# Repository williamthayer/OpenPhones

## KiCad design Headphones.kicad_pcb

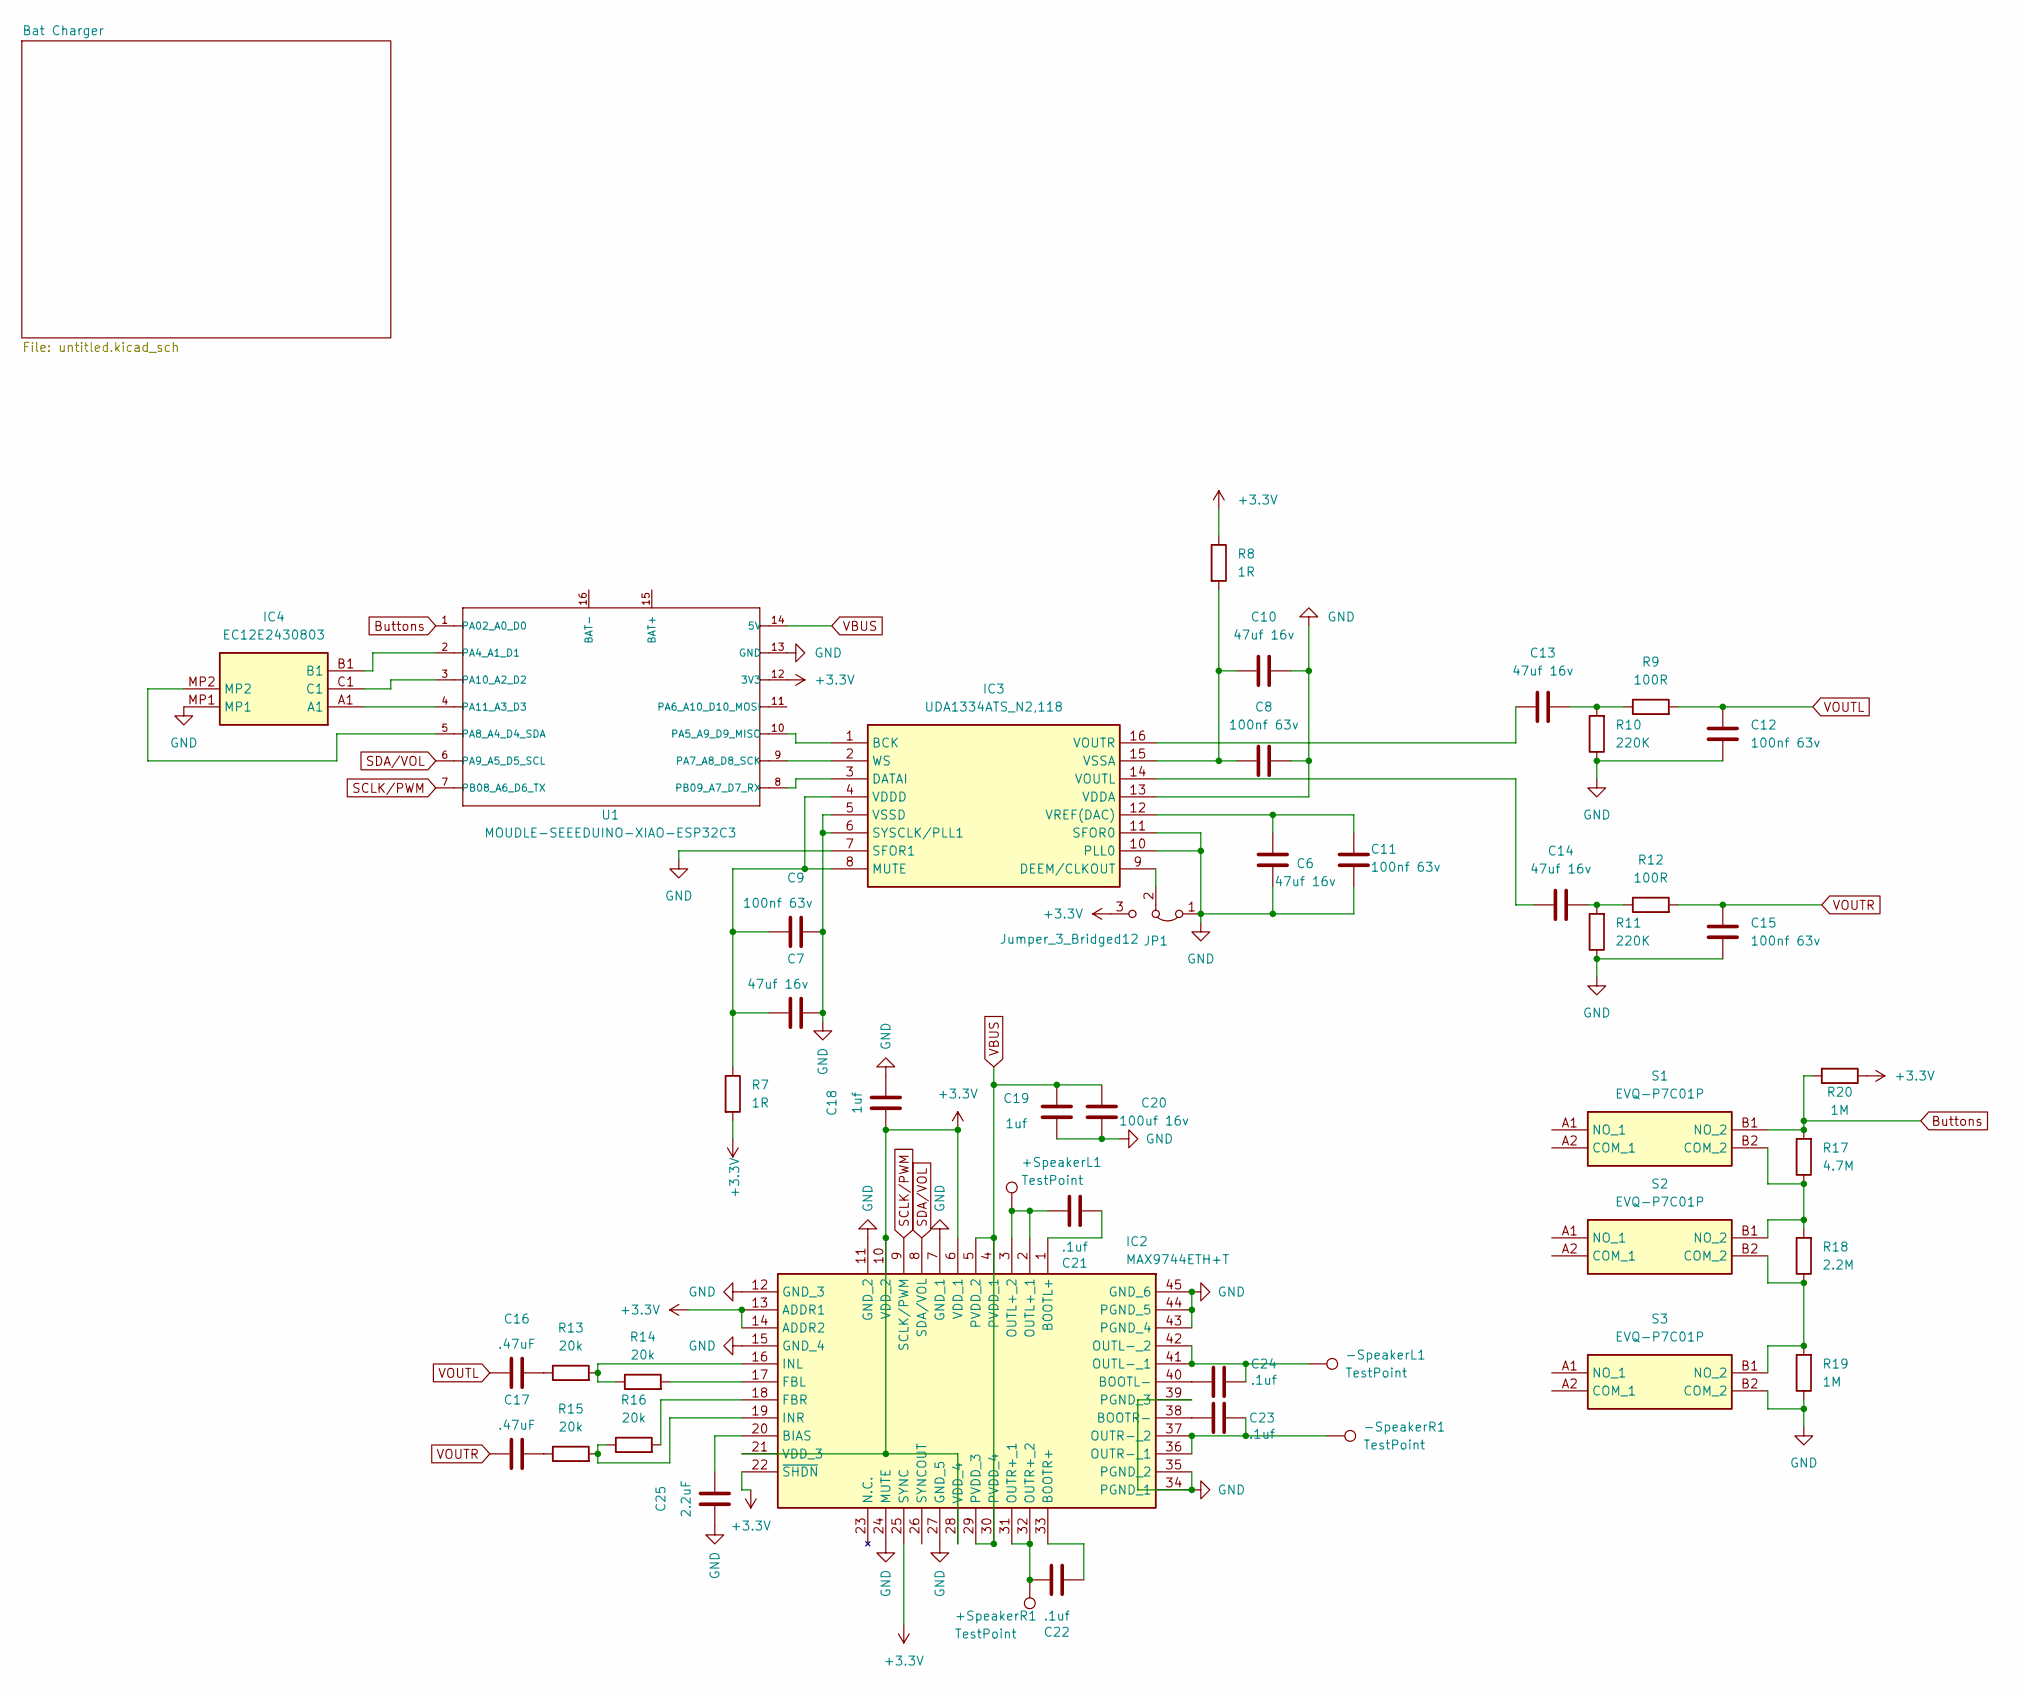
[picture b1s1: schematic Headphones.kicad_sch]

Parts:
+SpeakerL1: TestPoint; TestPoint_Loop_D1.80mm_Drill1.0mm_Beaded
+SpeakerR1: TestPoint; TestPoint_Loop_D1.80mm_Drill1.0mm_Beaded
-SpeakerL1: TestPoint; TestPoint_Loop_D1.80mm_Drill1.0mm_Beaded
-SpeakerR1: TestPoint; TestPoint_Loop_D1.80mm_Drill1.0mm_Beaded
C6, C7, C10, C13, C14: 47uf 16v; C_1210_3225Metric
C8, C9, C11, C12, C15: 100nf 63v; C_0805_2012Metric
C16, C17: .47uF; C_0805_2012Metric
C18, C19: 1uf; C_0805_2012Metric
C20: 100uf 16v; C_1210_3225Metric
C21, C22, C23, C24: .1uf; C_0805_2012Metric
C25: 2.2uF; C_0805_2012Metric
IC2: MAX9744ETH+T; QFN50P700X700X80-45N; Manufacturer_Part_Number MAX9744ETH+T; Mouser Part Number 700-MAX9744ETH+T
IC3: UDA1334ATS_N2,118; SOP65P640X150-16N; Manufacturer_Part_Number UDA1334ATS/N2,118; Mouser Part Number 771-UDA1334ATSDH-T
IC4: EC12E2430803; Manufacturer_Part_Number EC12E2430803; Mouser Part Number 688-EC12E2430803
JP1: Jumper_3_Bridged12; SolderJumper-3_P1.3mm_Bridged2Bar12_Pad1.0x1.5mm
R7, R8: 1R; R_0805_2012Metric
R9, R12: 100R; R_0805_2012Metric
R10, R11: 220K; R_0805_2012Metric
R13, R14, R15, R16: 20k; R_0805_2012Metric
R17: 4.7M; R_0805_2012Metric
R18: 2.2M; R_0805_2012Metric
R19, R20: 1M; R_0805_2012Metric
S1, S2, S3: EVQ-P7C01P; EVQP7C01P; Manufacturer_Part_Number EVQ-P7C01P; Mouser Part Number 667-EVQP7C01P
U1: MOUDLE-SEEEDUINO-XIAO-ESP32C3; MOUDLE14P-SMD-2.54-21X17.8MM

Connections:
+3.3V: C18.1, IC2.6 (VDD_1), IC2.10 (VDD_2), IC2.13 (ADDR1), IC2.14 (ADDR2), IC2.21 (VDD_3), IC2.22 (~SHDN), IC2.25 (SYNC), IC2.28 (VDD_4), JP1.3 (B), R7.2, R8.1, R20.1, U1.12 (3V3)
Buttons: R17.2, R20.2, S1.B1 (NO_2), U1.1 (PA02_A0_D0)
GND: C6.1, C7.2, C8.2, C9.2, C10.2, C11.1, C12.1, C15.1, C18.2, C19.1, C20.1, C25.1, IC2.7 (GND_1), IC2.11 (GND_2), IC2.12 (GND_3), IC2.15 (GND_4), IC2.24 (MUTE), IC2.27 (GND_5), IC2.34 (PGND_1), IC2.35 (PGND_2), IC2.39 (PGND_3), IC2.43 (PGND_4), IC2.44 (PGND_5), IC2.45 (GND_6), IC3.5 (VSSD), IC3.6 (SYSCLK/PLL1), IC3.7 (SFOR1), IC3.10 (PLL0), IC3.11 (SFOR0), IC3.13 (VDDA), IC4.MP1, JP1.1 (A), R10.1, R11.1, R19.1, S3.B2 (COM_2), U1.13 (GND); also elsewhere on the board
unnamed: C13.2, R9.1, R10.2
unnamed: C14.2, R11.2, R12.1
unnamed: C16.2, R13.1
unnamed: C17.2, R15.1
unnamed: C25.2, IC2.20 (BIAS)
unnamed: C21.1, IC2.1 (BOOTL+)
unnamed: C24.1, IC2.40 (BOOTL-)
unnamed: C22.1, IC2.33 (BOOTR+)
unnamed: C23.1, IC2.38 (BOOTR-)
unnamed: IC2.17 (FBL), R14.2
unnamed: IC2.18 (FBR), R16.2
unnamed: IC2.16 (INL), R13.2, R14.1
unnamed: IC2.19 (INR), R15.2, R16.1
unnamed: +SpeakerL1.1, C21.2, IC2.2 (OUTL+_1), IC2.3 (OUTL+_2)
unnamed: -SpeakerL1.1, C24.2, IC2.41 (OUTL-_1), IC2.42 (OUTL-_2)
unnamed: +SpeakerR1.1, C22.2, IC2.31 (OUTR+_1), IC2.32 (OUTR+_2)
unnamed: -SpeakerR1.1, C23.2, IC2.36 (OUTR-_1), IC2.37 (OUTR-_2)
unnamed: IC3.1 (BCK), U1.10 (PA5_A9_D9_MISO)
unnamed: IC3.3 (DATAI), U1.8 (PB09_A7_D7_RX)
unnamed: IC3.9 (DEEM/CLKOUT), JP1.2 (C)
unnamed: C7.1, C9.1, IC3.4 (VDDD), IC3.8 (MUTE), R7.1
unnamed: C14.1, IC3.14 (VOUTL)
unnamed: C13.1, IC3.16 (VOUTR)
unnamed: C6.2, C11.2, IC3.12 (VREF(DAC))
unnamed: C8.1, C10.1, IC3.15 (VSSA), R8.2
unnamed: IC3.2 (WS), U1.9 (PA7_A8_D8_SCK)
unnamed: R17.1, R18.2, S1.B2 (COM_2), S2.B1 (NO_2)
unnamed: R18.1, R19.2, S2.B2 (COM_2), S3.B1 (NO_2)
unnamed: IC4.B1, U1.2 (PA4_A1_D1)
unnamed: IC4.MP2, U1.5 (PA8_A4_D4_SDA)
unnamed: IC4.C1, U1.3 (PA10_A2_D2)
unnamed: IC4.A1, U1.4 (PA11_A3_D3)
SCLK/PWM: IC2.9 (SCLK/PWM), U1.7 (PB08_A6_D6_TX)
SDA/VOL: IC2.8 (SDA/VOL), U1.6 (PA9_A5_D5_SCL)
VBUS: C19.2, C20.2, IC2.4 (PVDD_1), IC2.5 (PVDD_2), IC2.29 (PVDD_3), IC2.30 (PVDD_4), U1.14 (5V); also elsewhere on the board
VOUTL: C12.2, C16.1, R9.2
VOUTR: C15.2, C17.1, R12.2

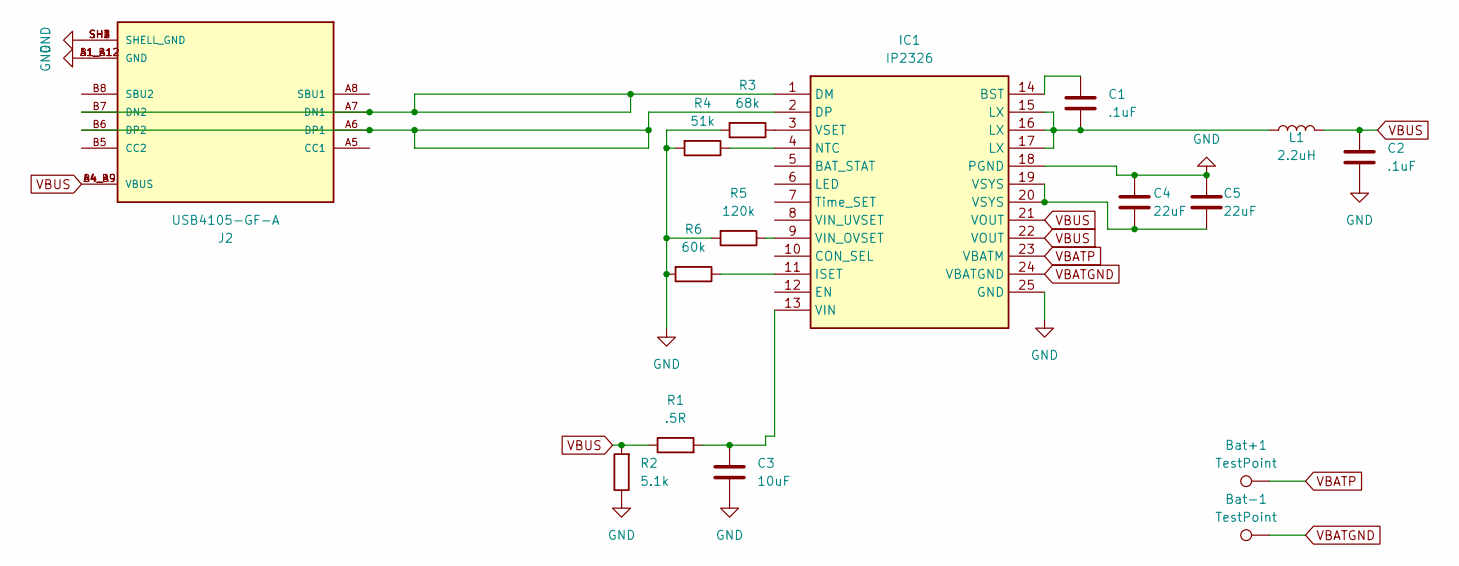
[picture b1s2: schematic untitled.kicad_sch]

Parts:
Bat+1: TestPoint; TestPoint_Loop_D1.80mm_Drill1.0mm_Beaded
Bat-1: TestPoint; TestPoint_Loop_D1.80mm_Drill1.0mm_Beaded
C1, C2: .1uF; C_0805_2012Metric
C3: 10uF; C_0805_2012Metric
C4, C5: 22uF; C_0805_2012Metric
IC1: IP2326; HVQFN-24-1EP_4x4mm_P0.5mm_EP2.5x2.5mm; Mouser Part Number 634-LB10F16ES1CFN24R
J2: USB4105-GF-A; GCT_USB4105-GF-A; PARTREV B4
L1: 2.2uH; L_0805_2012Metric
R1: .5R; R_0805_2012Metric
R2: 5.1k; R_0805_2012Metric
R3: 68k; R_0805_2012Metric
R4: 51k; R_0805_2012Metric
R5: 120k; R_0805_2012Metric
R6: 60k; R_0805_2012Metric

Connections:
GND: C2.2, C3.2, C4.1, C5.1, IC1.18 (PGND), IC1.25 (GND), J2.A1_B12 (GND), J2.B1_A12 (GND), J2.SH1 (SHELL_GND), J2.SH2 (SHELL_GND), J2.SH3 (SHELL_GND), J2.SH4 (SHELL_GND), R2.1, R3.2, R4.2, R5.2, R6.2; also elsewhere on the board
unnamed: C1.2, IC1.15 (LX), IC1.16 (LX), IC1.17 (LX), L1.1
unnamed: C4.2, C5.2, IC1.19 (VSYS), IC1.20 (VSYS)
unnamed: C1.1, IC1.14 (BST)
unnamed: IC1.1 (DM), J2.A7 (DN1), J2.B7 (DN2)
unnamed: IC1.2 (DP), J2.A6 (DP1), J2.B6 (DP2)
unnamed: IC1.11 (ISET), R6.1
unnamed: IC1.4 (NTC), R4.1
unnamed: C3.1, IC1.13 (VIN), R1.2
unnamed: IC1.9 (VIN_OVSET), R5.1
unnamed: IC1.3 (VSET), R3.1
VBATGND: Bat-1.1, IC1.24 (VBATGND)
VBATP: Bat+1.1, IC1.23 (VBATM)
VBUS: C2.1, IC1.21 (VOUT), IC1.22 (VOUT), J2.A4_B9 (VBUS), J2.B4_A9 (VBUS), L1.2, R1.1, R2.2; also elsewhere on the board

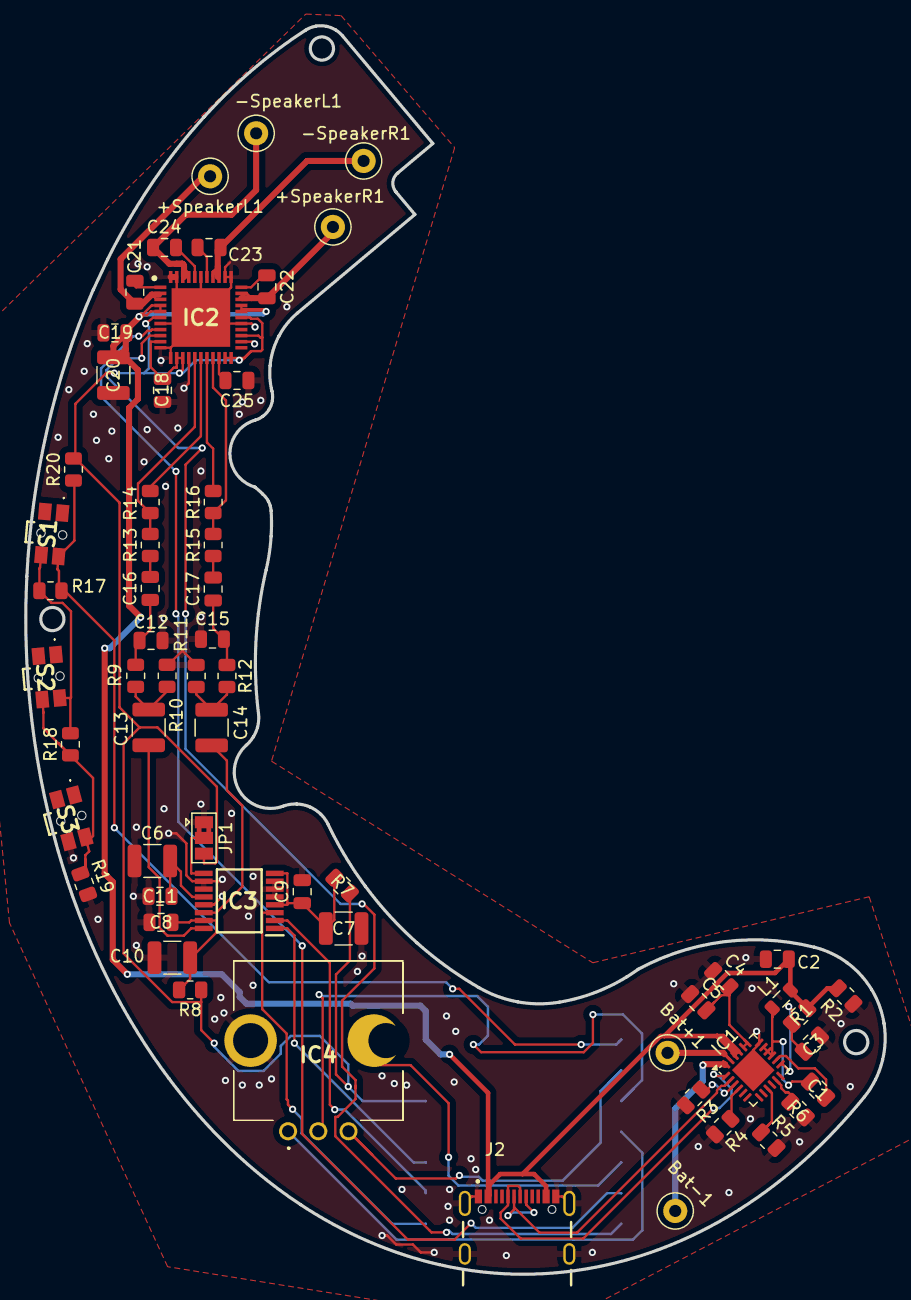
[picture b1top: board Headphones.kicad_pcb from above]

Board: 2 copper layers, 71.1 x 103.3 mm, 62 parts (1 on the bottom side), 52 nets.

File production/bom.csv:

Designator,Footprint,Quantity,Value,LCSC Part #
"+SPEAKERL1, +SPEAKERR1, -SPEAKERL1, -SPEAKERR1, BAT+1, BAT-1",TestPoint_Loop_D1.80mm_Drill1.0mm_Beaded,6,TestPoint,
"C1, C2, C21, C22, C23, C24",0805,6,.1uF,
"C10, C13, C14, C6, C7",1210,5,47uf 16v,
"C11, C12, C15, C8, C9",0805,5,100nf 63v,
"C16, C17",0805,2,.47uF,
"C18, C19",0805,2,1uf,
C20,1210,1,100uf 16v,
C25,0805,1,2.2uF,
C3,0805,1,10uF,
"C4, C5",0805,2,22uF,
IC1,HVQFN-24-1EP_4x4mm_P0.5mm_EP2.5x2.5mm,1,IP2326,
IC2,QFN50P700X700X80-45N,1,MAX9744ETH+T,
IC3,SOP65P640X150-16N,1,"UDA1334ATS_N2,118",
IC4,EC12E2430803,1,EC12E2430803,
J2,GCT_USB4105-GF-A,1,USB4105-GF-A,
L1,0805,1,2.2uH,
R1,0805,1,.5R,
"R10, R11",0805,2,220K,
"R12, R9",0805,2,100R,
"R13, R14, R15, R16",0805,4,20k,
R17,0805,1,4.7M,
R18,0805,1,2.2M,
"R19, R20",0805,2,1M,
R2,0805,1,5.1k,
R3,0805,1,68k,
R4,0805,1,51k,
R5,0805,1,120k,
R6,0805,1,60k,
"R7, R8",0805,2,1R,
"S1, S2, S3",EVQP7C01P,3,EVQ-P7C01P,
U1,MOUDLE14P-SMD-2.54-21X17.8MM,1,MOUDLE-SEEEDUINO-XIAO-ESP32C3,

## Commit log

2024-09-10 files
2024-09-10 Files upload
2024-11-27 Progress!
2024-11-27 Fixed broken files
2024-11-27 Minor updates
    Might need more room for the esp32. With the new USB connector the board space is very tight
2024-12-06 Rev1 Update
    Layout and traces done. 3d model done. Need to review layout placement and schematic. Change amp and dsp for lower cost??
